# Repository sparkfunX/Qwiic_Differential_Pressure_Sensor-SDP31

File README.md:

SparkX Differential Pressure Sensor - SDP31 (Qwiic)
===================================================

[*SparkX Differential Pressure Sensor - SDP31 (Qwiic) (SPX-17874)*](https://www.sparkfun.com/products/17874)

The SDP3x sensor family is Sensirion’s series of small differential pressure sensors designed for high-volume applications
where size is a key requirement. It builds on the next generation CMOSens® sensor chip that is at the heart of Sensirion’s
new differential pressure and flow sensing platform.

The digital SDP31 sensor features fast measurement speed, excellent accuracy and long-term stability and has no zero-point
drift. Furthermore, it is reflow solderable and provides extended functionality, such as smart averaging, multiple temperature
compensation modes, configurable I2C address and interrupts.

Able to measure differential pressures in the range +/- 500 Pascals (+/- 0.005 Atm), the SDP31 is ideally suited to air flow rate
and air speed measurement. Need an air speed indicator for your drone or model aircraft? This could be the sensor for you!

Repository Contents
-------------------
* **/Documents** - datasheets etc.
* **/Hardware** - Eagle design files (.brd, .sch)

Documentation
--------------
* **[SDP3X Arduino Library](https://github.com/sparkfun/SparkFun_SDP3x_Arduino_Library)** - Arduino library for the SparkFun Differential Pressure Sensor - SDP31.
* **[Hookup Guide]()** - Basic hookup guide for the SparkX Differential Pressure Sensor - SDP31.

Product Versions
----------------
* [SPX-17874](https://www.sparkfun.com/products/17874) - Original SparkX Release.

License Information
-------------------

This product is _**open source**_!

Please review the LICENSE.md file for license information.

If you have any questions or concerns on licensing, please contact technical support on our [SparkFun forums](https://forum.sparkfun.com/viewforum.php?f=152).

Distributed as-is; no warranty is given.

- Your friends at SparkFun.

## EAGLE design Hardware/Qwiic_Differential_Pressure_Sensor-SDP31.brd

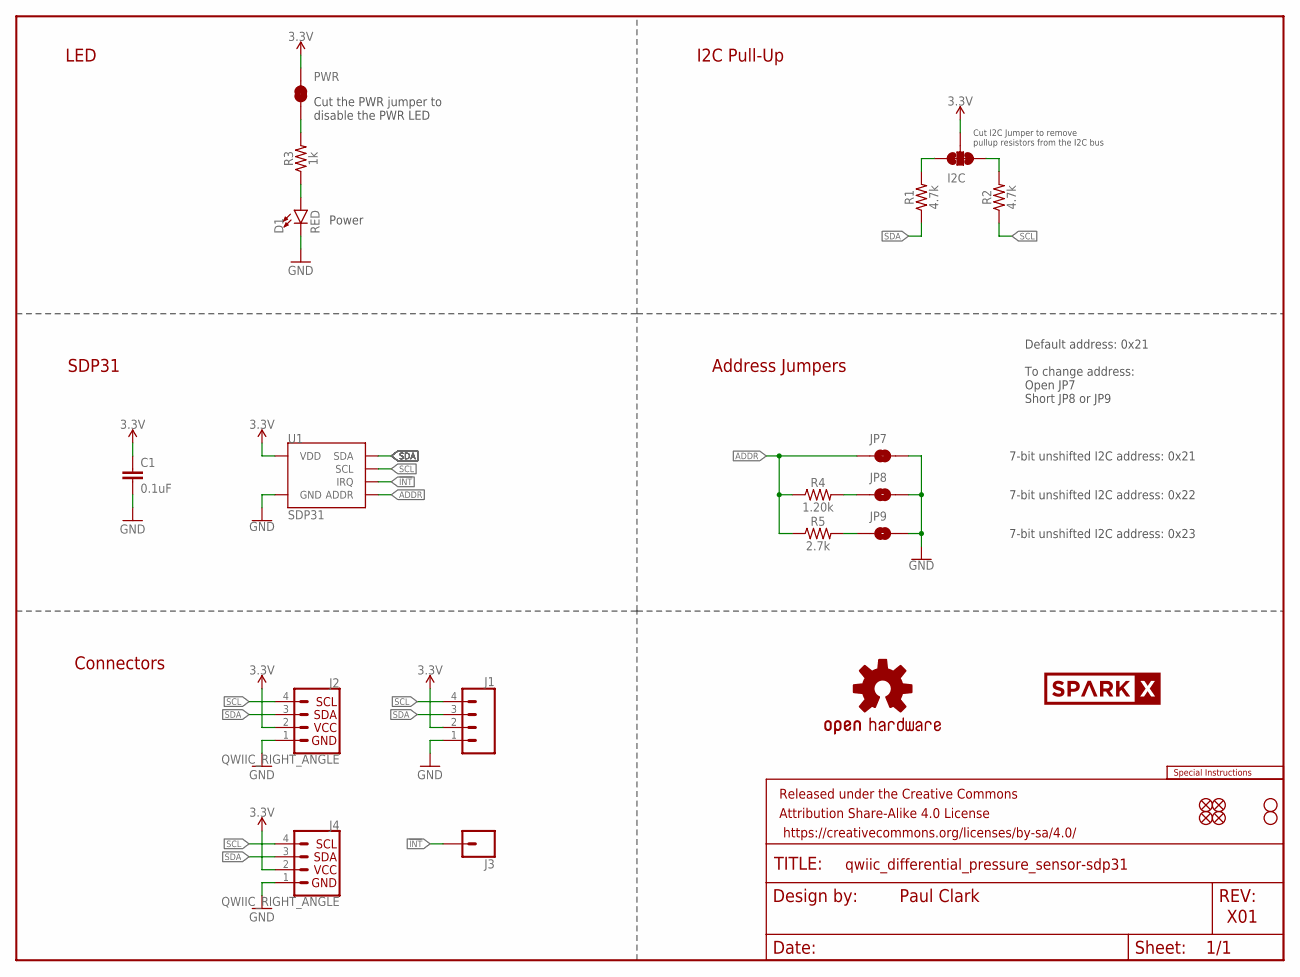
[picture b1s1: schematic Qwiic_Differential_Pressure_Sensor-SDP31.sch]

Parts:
C1: 0.1uF; 0603
D1: RED; LED-0603
FRAME1: FRAME-LETTER; CREATIVE_COMMONS
I2C: JUMPER-SMT_3_2-NC_TRACE_SILK; SMT-JUMPER_3_2-NC_TRACE_SILK
J1: CONN_041X04_NO_SILK; 1X04_NO_SILK
J2, J4: QWIIC_RIGHT_ANGLE; JST04_1MM_RA
J3: CONN_01PTH_NO_SILK_YES_STOP; 1X01_NO_SILK
JP1, JP2, JP5, JP6: FIDUCIALUFIDUCIAL; FIDUCIAL-MICRO
JP3, JP4: STAND-OFF
JP7: JUMPER-SMT_2_NC_TRACE_SILK; SMT-JUMPER_2_NC_TRACE_SILK
JP8, JP9: JUMPER-SMT_2_NO_SILK; SMT-JUMPER_2_NO_SILK
LOGO1: SPECIAL_INSTRUCTIONS-ORDERING; ORDERING_INSTRUCTIONS
LOGO5: OSHW-LOGOS; OSHW-LOGO-S
PWR: JUMPER-SMT_2_NC_TRACE_SILK; SMT-JUMPER_2_NC_TRACE_SILK
R1, R2: 4.7k; 0603
R3: 1k; 0603
R4: 1.20k; 0603
R5: 2.7k; 0603
U1: SDP31; SDP3X
U$18: SPARKX-LOGO3; SPARKX-SMALL

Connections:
3.3V: C1.1, I2C.2, J1.2, J2.2, J4.2, PWR.2, U1.7 (VDD)
!INT!: J3.1, U1.4 (IRQ)
ADDR: JP7.1, R4.1, R5.1, U1.9 (ADDR)
GND: C1.2, D1.C, J1.1, J2.1, J4.1, JP7.2, JP8.2, JP9.2, U1.1 (GND), U1.2 (GND), U1.3 (GND), U1.6 (GND), U1.10 (GND), U1.11 (GND), U1.DIEPAD1 (GND), U1.DIEPAD2 (GND)
unnamed: PWR.1, R3.2
unnamed: I2C.3, R1.2
unnamed: D1.A, R3.1
unnamed: I2C.1, R2.2
unnamed: JP8.1, R4.2
unnamed: JP9.1, R5.2
SCL: J1.4, J2.4, J4.4, R2.1, U1.5 (SCL)
SDA: J1.3, J2.3, J4.3, R1.1, U1.8 (SDA)

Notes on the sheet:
Paul Clark
X01
7-bit unshifted I2C address: 0x21
Power
I2C Pull-Up
SDP31
Connectors
Cut the PWR jumper to disable the PWR LED
Cut I2C Jumper to remove pullup resistors from the I2C bus
LED
Address Jumpers
7-bit unshifted I2C address: 0x22
7-bit unshifted I2C address: 0x23
Default address: 0x21 To change address: Open JP7 Short JP8 or JP9

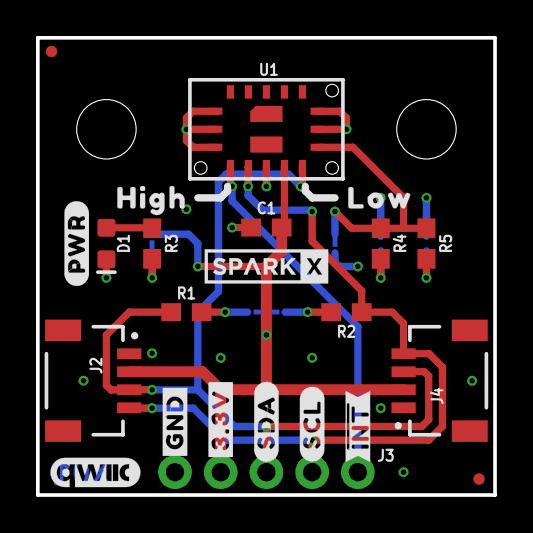
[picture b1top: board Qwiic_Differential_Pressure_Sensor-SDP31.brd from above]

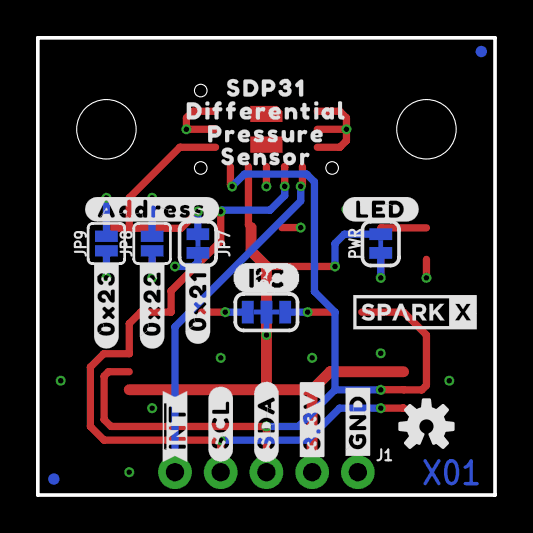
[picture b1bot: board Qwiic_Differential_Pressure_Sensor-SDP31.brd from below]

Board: 4 copper layers, 25.4 x 25.4 mm, 52 parts (25 on the bottom side), 12 nets.

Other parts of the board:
U$1, U$33: #GND#0
U$2, U$34: #3#3V#0
U$3, U$35: #SDA#0
U$4, U$36: #SCL#0
U$5, U$6: ##INT##0
U$7: #0X21#0
U$8: #0X22#0
U$9: #0X23#0
U$10: DIFFERENTIAL0
U$11: PRESSURE0
U$12: SENSOR0
U$13: SDP310
U$14: #LED#0
U$15: I2C
U$16: QWIIC_5MM
U$17: HIGH0
U$19: LOW0
U$20: SPARKX-LOGO3; SPARKX-SMALL
U$21: #ADDRESS#0
U$32: #PWR#0

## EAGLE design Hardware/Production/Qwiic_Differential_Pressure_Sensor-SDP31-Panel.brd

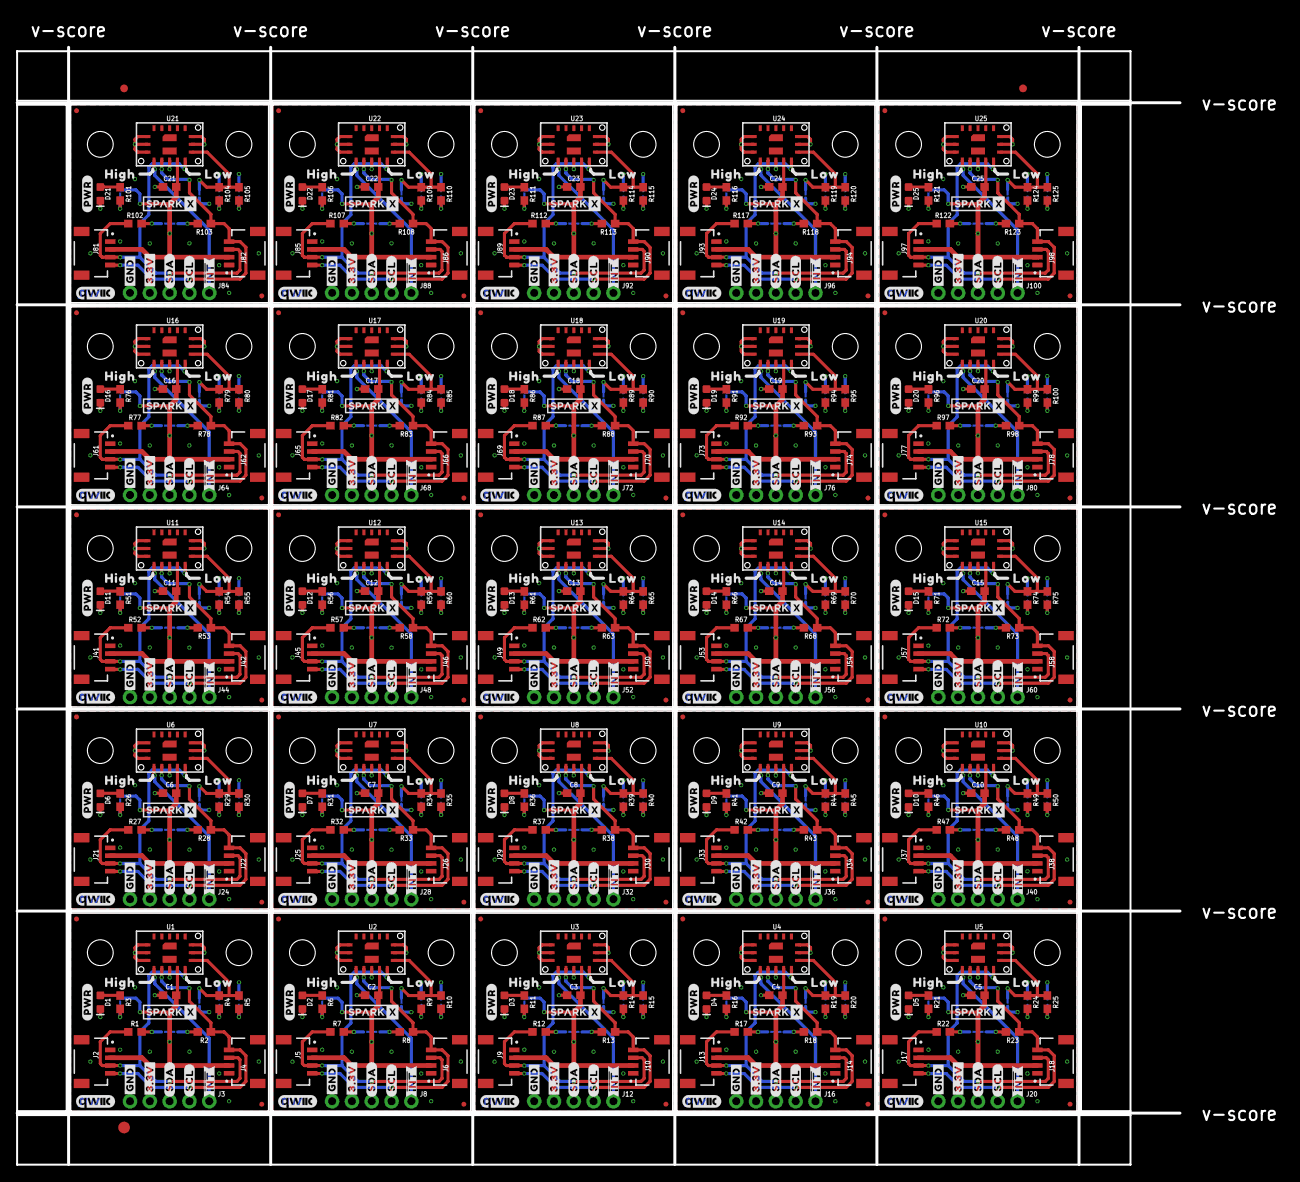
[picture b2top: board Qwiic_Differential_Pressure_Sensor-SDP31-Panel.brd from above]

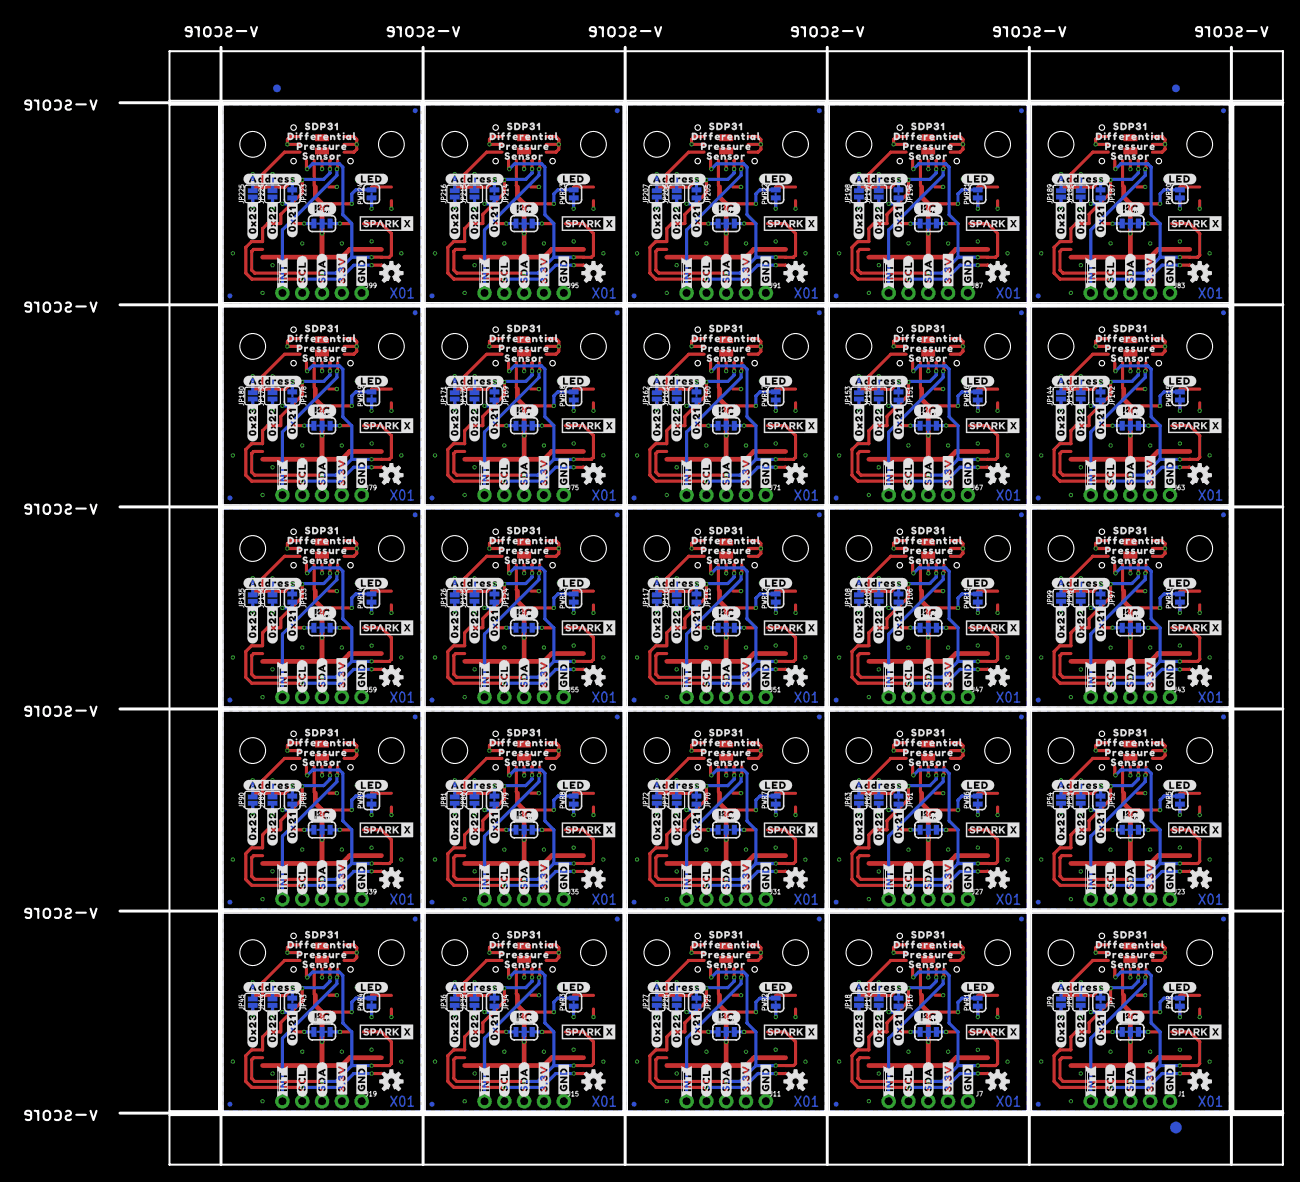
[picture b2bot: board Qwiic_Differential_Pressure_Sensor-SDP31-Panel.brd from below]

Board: 4 copper layers, 162.3 x 147.1 mm, 1256 parts (628 on the bottom side), 300 nets.

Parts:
C1, C2, C3, C4, C5, C6, C7, C8, C9, C10, C11, C12, C13, C14, C15, C16, C17, C18, C19, C20, C21, C22, C23, C24, C25: 0.1uF; 0603
D1, D2, D3, D4, D5, D6, D7, D8, D9, D10, D11, D12, D13, D14, D15, D16, D17, D18, D19, D20, D21, D22, D23, D24, D25: RED; LED-0603
E$1, E$2, E$3, E$4: FIDUCIAL-1X2
E$5, E$6: FIDUCIAL-1.5X3
I2C, I2C1, I2C2, I2C3, I2C4, I2C5, I2C6, I2C7, I2C8, I2C9, I2C10, I2C11, I2C12, I2C13, I2C14, I2C15, I2C16, I2C17, I2C18, I2C19, I2C20, I2C21, I2C22, I2C23, I2C24: JUMPER-SMT_3_2-NC_TRACE_SILK; SMT-JUMPER_3_2-NC_TRACE_SILK
J1, J7, J11, J15, J19, J23, J27, J31, J35, J39, J43, J47, J51, J55, J59, J63, J67, J71, J75, J79, J83, J87, J91, J95, J99: 1X04_NO_SILK
J2, J4, J5, J6, J9, J10, J13, J14, J17, J18, J21, J22, J25, J26, J29, J30, J33, J34, J37, J38, J41, J42, J45, J46, J49, J50, J53, J54, J57, J58, J61, J62, J65, J66, J69, J70, J73, J74, J77, J78, J81, J82, J85, J86, J89, J90, J93, J94, J97, J98: QWIIC_RIGHT_ANGLE; JST04_1MM_RA
J3, J8, J12, J16, J20, J24, J28, J32, J36, J40, J44, J48, J52, J56, J60, J64, J68, J72, J76, J80, J84, J88, J92, J96, J100: 1X01_NO_SILK
JP1, JP2, JP5, JP6, JP12, JP13, JP14, JP15, JP21, JP22, JP23, JP24, JP30, JP31, JP32, JP33, JP39, JP40, JP41, JP42, JP48, JP49, JP50, JP51, JP57, JP58, JP59, JP60, JP66, JP67, JP68, JP69, JP75, JP76, JP77, JP78, JP84, JP85, JP86, JP87, JP93, JP94, JP95, JP96, JP102, JP103, JP104, JP105, JP111, JP112, JP113, JP114, JP120, JP121, JP122, JP123, JP129, JP130, JP131, JP132, JP138, JP139, JP140, JP141, JP147, JP148, JP149, JP150, JP156, JP157, JP158, JP159, JP165, JP166, JP167, JP168, JP174, JP175, JP176, JP177, JP183, JP184, JP185, JP186, JP192, JP193, JP194, JP195, JP201, JP202, JP203, JP204, JP210, JP211, JP212, JP213, JP219, JP220, JP221, JP222: FIDUCIALUFIDUCIAL; FIDUCIAL-MICRO
JP3, JP4, JP10, JP11, JP19, JP20, JP28, JP29, JP37, JP38, JP46, JP47, JP55, JP56, JP64, JP65, JP73, JP74, JP82, JP83, JP91, JP92, JP100, JP101, JP109, JP110, JP118, JP119, JP127, JP128, JP136, JP137, JP145, JP146, JP154, JP155, JP163, JP164, JP172, JP173, JP181, JP182, JP190, JP191, JP199, JP200, JP208, JP209, JP217, JP218: STAND-OFF
JP7, JP16, JP25, JP34, JP43, JP52, JP61, JP70, JP79, JP88, JP97, JP106, JP115, JP124, JP133, JP142, JP151, JP160, JP169, JP178, JP187, JP196, JP205, JP214, JP223: JUMPER-SMT_2_NC_TRACE_SILK; SMT-JUMPER_2_NC_TRACE_SILK
JP8, JP9, JP17, JP18, JP26, JP27, JP35, JP36, JP44, JP45, JP53, JP54, JP62, JP63, JP71, JP72, JP80, JP81, JP89, JP90, JP98, JP99, JP107, JP108, JP116, JP117, JP125, JP126, JP134, JP135, JP143, JP144, JP152, JP153, JP161, JP162, JP170, JP171, JP179, JP180, JP188, JP189, JP197, JP198, JP206, JP207, JP215, JP216, JP224, JP225: JUMPER-SMT_2_NO_SILK; SMT-JUMPER_2_NO_SILK
LOGO1, LOGO2, LOGO3, LOGO4, LOGO5, LOGO6, LOGO7, LOGO8, LOGO9, LOGO10, LOGO11, LOGO12, LOGO13, LOGO14, LOGO15, LOGO16, LOGO17, LOGO18, LOGO19, LOGO20, LOGO21, LOGO22, LOGO23, LOGO24, LOGO25: OSHW-LOGOS; OSHW-LOGO-S
PWR, PWR1, PWR2, PWR3, PWR4, PWR5, PWR6, PWR7, PWR8, PWR9, PWR10, PWR11, PWR12, PWR13, PWR14, PWR15, PWR16, PWR17, PWR18, PWR19, PWR20, PWR21, PWR22, PWR23, PWR24: JUMPER-SMT_2_NC_TRACE_SILK; SMT-JUMPER_2_NC_TRACE_SILK
R1, R2, R7, R8, R12, R13, R17, R18, R22, R23, R27, R28, R32, R33, R37, R38, R42, R43, R47, R48, R52, R53, R57, R58, R62, R63, R67, R68, R72, R73, R77, R78, R82, R83, R87, R88, R92, R93, R97, R98, R102, R103, R107, R108, R112, R113, R117, R118, R122, R123: 4.7k; 0603
R3, R6, R11, R16, R21, R26, R31, R36, R41, R46, R51, R56, R61, R66, R71, R76, R81, R86, R91, R96, R101, R106, R111, R116, R121: 1k; 0603
R4, R9, R14, R19, R24, R29, R34, R39, R44, R49, R54, R59, R64, R69, R74, R79, R84, R89, R94, R99, R104, R109, R114, R119, R124: 1.20k; 0603
R5, R10, R15, R20, R25, R30, R35, R40, R45, R50, R55, R60, R65, R70, R75, R80, R85, R90, R95, R100, R105, R110, R115, R120, R125: 2.7k; 0603
U1, U2, U3, U4, U5, U6, U7, U8, U9, U10, U11, U12, U13, U14, U15, U16, U17, U18, U19, U20, U21, U22, U23, U24, U25: SDP31; SDP3X
U$1, U$26, U$30, U$33, U$57, U$61, U$83, U$87, U$109, U$113, U$135, U$139, U$161, U$165, U$187, U$191, U$213, U$217, U$239, U$243, U$265, U$269, U$291, U$295, U$317, U$321, U$343, U$347, U$369, U$373, U$395, U$399, U$421, U$425, U$447, U$451, U$473, U$477, U$499, U$503, U$525, U$529, U$551, U$555, U$577, U$581, U$603, U$607, U$629, U$633: #GND#0
U$2, U$27, U$31, U$34, U$58, U$62, U$84, U$88, U$110, U$114, U$136, U$140, U$162, U$166, U$188, U$192, U$214, U$218, U$240, U$244, U$266, U$270, U$292, U$296, U$318, U$322, U$344, U$348, U$370, U$374, U$396, U$400, U$422, U$426, U$448, U$452, U$474, U$478, U$500, U$504, U$526, U$530, U$552, U$556, U$578, U$582, U$604, U$608, U$630, U$634: #3#3V#0
U$3, U$28, U$35, U$37, U$59, U$63, U$85, U$89, U$111, U$115, U$137, U$141, U$163, U$167, U$189, U$193, U$215, U$219, U$241, U$245, U$267, U$271, U$293, U$297, U$319, U$323, U$345, U$349, U$371, U$375, U$397, U$401, U$423, U$427, U$449, U$453, U$475, U$479, U$501, U$505, U$527, U$531, U$553, U$557, U$579, U$583, U$605, U$609, U$631, U$635: #SDA#0
U$4, U$29, U$36, U$38, U$60, U$64, U$86, U$90, U$112, U$116, U$138, U$142, U$164, U$168, U$190, U$194, U$216, U$220, U$242, U$246, U$268, U$272, U$294, U$298, U$320, U$324, U$346, U$350, U$372, U$376, U$398, U$402, U$424, U$428, U$450, U$454, U$476, U$480, U$502, U$506, U$528, U$532, U$554, U$558, U$580, U$584, U$606, U$610, U$632, U$636: #SCL#0
U$5, U$6, U$50, U$51, U$76, U$77, U$102, U$103, U$128, U$129, U$154, U$155, U$180, U$181, U$206, U$207, U$232, U$233, U$258, U$259, U$284, U$285, U$310, U$311, U$336, U$337, U$362, U$363, U$388, U$389, U$414, U$415, U$440, U$441, U$466, U$467, U$492, U$493, U$518, U$519, U$544, U$545, U$570, U$571, U$596, U$597, U$622, U$623, U$648, U$649: ##INT##0
U$7, U$39, U$65, U$91, U$117, U$143, U$169, U$195, U$221, U$247, U$273, U$299, U$325, U$351, U$377, U$403, U$429, U$455, U$481, U$507, U$533, U$559, U$585, U$611, U$637: #0X21#0
U$8, U$40, U$66, U$92, U$118, U$144, U$170, U$196, U$222, U$248, U$274, U$300, U$326, U$352, U$378, U$404, U$430, U$456, U$482, U$508, U$534, U$560, U$586, U$612, U$638: #0X22#0
U$9, U$41, U$67, U$93, U$119, U$145, U$171, U$197, U$223, U$249, U$275, U$301, U$327, U$353, U$379, U$405, U$431, U$457, U$483, U$509, U$535, U$561, U$587, U$613, U$639: #0X23#0
U$10, U$42, U$68, U$94, U$120, U$146, U$172, U$198, U$224, U$250, U$276, U$302, U$328, U$354, U$380, U$406, U$432, U$458, U$484, U$510, U$536, U$562, U$588, U$614, U$640: DIFFERENTIAL0
U$11, U$43, U$69, U$95, U$121, U$147, U$173, U$199, U$225, U$251, U$277, U$303, U$329, U$355, U$381, U$407, U$433, U$459, U$485, U$511, U$537, U$563, U$589, U$615, U$641: PRESSURE0
U$12, U$44, U$70, U$96, U$122, U$148, U$174, U$200, U$226, U$252, U$278, U$304, U$330, U$356, U$382, U$408, U$434, U$460, U$486, U$512, U$538, U$564, U$590, U$616, U$642: SENSOR0
U$13, U$45, U$71, U$97, U$123, U$149, U$175, U$201, U$227, U$253, U$279, U$305, U$331, U$357, U$383, U$409, U$435, U$461, U$487, U$513, U$539, U$565, U$591, U$617, U$643: SDP310
U$14, U$46, U$72, U$98, U$124, U$150, U$176, U$202, U$228, U$254, U$280, U$306, U$332, U$358, U$384, U$410, U$436, U$462, U$488, U$514, U$540, U$566, U$592, U$618, U$644: #LED#0
U$15, U$22, U$53, U$79, U$105, U$131, U$157, U$183, U$209, U$235, U$261, U$287, U$313, U$339, U$365, U$391, U$417, U$443, U$469, U$495, U$521, U$547, U$573, U$599, U$625: I2C
U$16, U$23, U$54, U$80, U$106, U$132, U$158, U$184, U$210, U$236, U$262, U$288, U$314, U$340, U$366, U$392, U$418, U$444, U$470, U$496, U$522, U$548, U$574, U$600, U$626: QWIIC_5MM
U$17, U$47, U$73, U$99, U$125, U$151, U$177, U$203, U$229, U$255, U$281, U$307, U$333, U$359, U$385, U$411, U$437, U$463, U$489, U$515, U$541, U$567, U$593, U$619, U$645: HIGH0
U$18, U$20, U$24, U$49, U$55, U$75, U$81, U$101, U$107, U$127, U$133, U$153, U$159, U$179, U$185, U$205, U$211, U$231, U$237, U$257, U$263, U$283, U$289, U$309, U$315, U$335, U$341, U$361, U$367, U$387, U$393, U$413, U$419, U$439, U$445, U$465, U$471, U$491, U$497, U$517, U$523, U$543, U$549, U$569, U$575, U$595, U$601, U$621, U$627, U$647: SPARKX-LOGO3; SPARKX-SMALL
U$19, U$48, U$74, U$100, U$126, U$152, U$178, U$204, U$230, U$256, U$282, U$308, U$334, U$360, U$386, U$412, U$438, U$464, U$490, U$516, U$542, U$568, U$594, U$620, U$646: LOW0
U$21, U$52, U$78, U$104, U$130, U$156, U$182, U$208, U$234, U$260, U$286, U$312, U$338, U$364, U$390, U$416, U$442, U$468, U$494, U$520, U$546, U$572, U$598, U$624, U$650: #ADDRESS#0
U$25, U$32, U$56, U$82, U$108, U$134, U$160, U$186, U$212, U$238, U$264, U$290, U$316, U$342, U$368, U$394, U$420, U$446, U$472, U$498, U$524, U$550, U$576, U$602, U$628: #PWR#0

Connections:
3.3V: C1.1, I2C.2, J1.2, J2.2, J4.2, PWR.2, U1.7
3.3V1: C2.1, I2C1.2, J5.2, J6.2, J7.2, PWR1.2, U2.7
3.3V2: C3.1, I2C2.2, J9.2, J10.2, J11.2, PWR2.2, U3.7
3.3V3: C4.1, I2C3.2, J13.2, J14.2, J15.2, PWR3.2, U4.7
3.3V4: C5.1, I2C4.2, J17.2, J18.2, J19.2, PWR4.2, U5.7
3.3V5: C6.1, I2C5.2, J21.2, J22.2, J23.2, PWR5.2, U6.7
3.3V6: C7.1, I2C6.2, J25.2, J26.2, J27.2, PWR6.2, U7.7
3.3V7: C8.1, I2C7.2, J29.2, J30.2, J31.2, PWR7.2, U8.7
3.3V8: C9.1, I2C8.2, J33.2, J34.2, J35.2, PWR8.2, U9.7
3.3V9: C10.1, I2C9.2, J37.2, J38.2, J39.2, PWR9.2, U10.7
3.3V10: C11.1, I2C10.2, J41.2, J42.2, J43.2, PWR10.2, U11.7
3.3V11: C12.1, I2C11.2, J45.2, J46.2, J47.2, PWR11.2, U12.7
3.3V12: C13.1, I2C12.2, J49.2, J50.2, J51.2, PWR12.2, U13.7
3.3V13: C14.1, I2C13.2, J53.2, J54.2, J55.2, PWR13.2, U14.7
3.3V14: C15.1, I2C14.2, J57.2, J58.2, J59.2, PWR14.2, U15.7
3.3V15: C16.1, I2C15.2, J61.2, J62.2, J63.2, PWR15.2, U16.7
3.3V16: C17.1, I2C16.2, J65.2, J66.2, J67.2, PWR16.2, U17.7
3.3V17: C18.1, I2C17.2, J69.2, J70.2, J71.2, PWR17.2, U18.7
3.3V18: C19.1, I2C18.2, J73.2, J74.2, J75.2, PWR18.2, U19.7
3.3V19: C20.1, I2C19.2, J77.2, J78.2, J79.2, PWR19.2, U20.7
3.3V20: C21.1, I2C20.2, J81.2, J82.2, J83.2, PWR20.2, U21.7
3.3V21: C22.1, I2C21.2, J85.2, J86.2, J87.2, PWR21.2, U22.7
3.3V22: C23.1, I2C22.2, J89.2, J90.2, J91.2, PWR22.2, U23.7
3.3V23: C24.1, I2C23.2, J93.2, J94.2, J95.2, PWR23.2, U24.7
3.3V24: C25.1, I2C24.2, J97.2, J98.2, J99.2, PWR24.2, U25.7
!INT!: J3.1, U1.4
!INT!1: J8.1, U2.4
!INT!2: J12.1, U3.4
!INT!3: J16.1, U4.4
!INT!4: J20.1, U5.4
!INT!5: J24.1, U6.4
!INT!6: J28.1, U7.4
!INT!7: J32.1, U8.4
!INT!8: J36.1, U9.4
!INT!9: J40.1, U10.4
!INT!10: J44.1, U11.4
!INT!11: J48.1, U12.4
!INT!12: J52.1, U13.4
!INT!13: J56.1, U14.4
!INT!14: J60.1, U15.4
!INT!15: J64.1, U16.4
!INT!16: J68.1, U17.4
!INT!17: J72.1, U18.4
!INT!18: J76.1, U19.4
!INT!19: J80.1, U20.4
!INT!20: J84.1, U21.4
!INT!21: J88.1, U22.4
!INT!22: J92.1, U23.4
!INT!23: J96.1, U24.4
!INT!24: J100.1, U25.4
ADDR: JP7.1, R4.1, R5.1, U1.9
ADDR1: JP16.1, R9.1, R10.1, U2.9
ADDR2: JP25.1, R14.1, R15.1, U3.9
ADDR3: JP34.1, R19.1, R20.1, U4.9
ADDR4: JP43.1, R24.1, R25.1, U5.9
ADDR5: JP52.1, R29.1, R30.1, U6.9
ADDR6: JP61.1, R34.1, R35.1, U7.9
ADDR7: JP70.1, R39.1, R40.1, U8.9
ADDR8: JP79.1, R44.1, R45.1, U9.9
ADDR9: JP88.1, R49.1, R50.1, U10.9
ADDR10: JP97.1, R54.1, R55.1, U11.9
ADDR11: JP106.1, R59.1, R60.1, U12.9
ADDR12: JP115.1, R64.1, R65.1, U13.9
ADDR13: JP124.1, R69.1, R70.1, U14.9
ADDR14: JP133.1, R74.1, R75.1, U15.9
ADDR15: JP142.1, R79.1, R80.1, U16.9
ADDR16: JP151.1, R84.1, R85.1, U17.9
ADDR17: JP160.1, R89.1, R90.1, U18.9
ADDR18: JP169.1, R94.1, R95.1, U19.9
ADDR19: JP178.1, R99.1, R100.1, U20.9
ADDR20: JP187.1, R104.1, R105.1, U21.9
ADDR21: JP196.1, R109.1, R110.1, U22.9
ADDR22: JP205.1, R114.1, R115.1, U23.9
ADDR23: JP214.1, R119.1, R120.1, U24.9
ADDR24: JP223.1, R124.1, R125.1, U25.9
GND: C1.2, D1.C, J1.1, J2.1, J4.1, JP7.2, JP8.2, JP9.2, U1.1, U1.2, U1.3, U1.6, U1.10, U1.11, U1.DIEPAD1, U1.DIEPAD2
GND1: C2.2, D2.C, J5.1, J6.1, J7.1, JP16.2, JP17.2, JP18.2, U2.1, U2.2, U2.3, U2.6, U2.10, U2.11, U2.DIEPAD1, U2.DIEPAD2
GND2: C3.2, D3.C, J9.1, J10.1, J11.1, JP25.2, JP26.2, JP27.2, U3.1, U3.2, U3.3, U3.6, U3.10, U3.11, U3.DIEPAD1, U3.DIEPAD2
GND3: C4.2, D4.C, J13.1, J14.1, J15.1, JP34.2, JP35.2, JP36.2, U4.1, U4.2, U4.3, U4.6, U4.10, U4.11, U4.DIEPAD1, U4.DIEPAD2
GND4: C5.2, D5.C, J17.1, J18.1, J19.1, JP43.2, JP44.2, JP45.2, U5.1, U5.2, U5.3, U5.6, U5.10, U5.11, U5.DIEPAD1, U5.DIEPAD2
GND5: C6.2, D6.C, J21.1, J22.1, J23.1, JP52.2, JP53.2, JP54.2, U6.1, U6.2, U6.3, U6.6, U6.10, U6.11, U6.DIEPAD1, U6.DIEPAD2
GND6: C7.2, D7.C, J25.1, J26.1, J27.1, JP61.2, JP62.2, JP63.2, U7.1, U7.2, U7.3, U7.6, U7.10, U7.11, U7.DIEPAD1, U7.DIEPAD2
GND7: C8.2, D8.C, J29.1, J30.1, J31.1, JP70.2, JP71.2, JP72.2, U8.1, U8.2, U8.3, U8.6, U8.10, U8.11, U8.DIEPAD1, U8.DIEPAD2
GND8: C9.2, D9.C, J33.1, J34.1, J35.1, JP79.2, JP80.2, JP81.2, U9.1, U9.2, U9.3, U9.6, U9.10, U9.11, U9.DIEPAD1, U9.DIEPAD2
GND9: C10.2, D10.C, J37.1, J38.1, J39.1, JP88.2, JP89.2, JP90.2, U10.1, U10.2, U10.3, U10.6, U10.10, U10.11, U10.DIEPAD1, U10.DIEPAD2
GND10: C11.2, D11.C, J41.1, J42.1, J43.1, JP97.2, JP98.2, JP99.2, U11.1, U11.2, U11.3, U11.6, U11.10, U11.11, U11.DIEPAD1, U11.DIEPAD2
GND11: C12.2, D12.C, J45.1, J46.1, J47.1, JP106.2, JP107.2, JP108.2, U12.1, U12.2, U12.3, U12.6, U12.10, U12.11, U12.DIEPAD1, U12.DIEPAD2
GND12: C13.2, D13.C, J49.1, J50.1, J51.1, JP115.2, JP116.2, JP117.2, U13.1, U13.2, U13.3, U13.6, U13.10, U13.11, U13.DIEPAD1, U13.DIEPAD2
GND13: C14.2, D14.C, J53.1, J54.1, J55.1, JP124.2, JP125.2, JP126.2, U14.1, U14.2, U14.3, U14.6, U14.10, U14.11, U14.DIEPAD1, U14.DIEPAD2
GND14: C15.2, D15.C, J57.1, J58.1, J59.1, JP133.2, JP134.2, JP135.2, U15.1, U15.2, U15.3, U15.6, U15.10, U15.11, U15.DIEPAD1, U15.DIEPAD2
GND15: C16.2, D16.C, J61.1, J62.1, J63.1, JP142.2, JP143.2, JP144.2, U16.1, U16.2, U16.3, U16.6, U16.10, U16.11, U16.DIEPAD1, U16.DIEPAD2
GND16: C17.2, D17.C, J65.1, J66.1, J67.1, JP151.2, JP152.2, JP153.2, U17.1, U17.2, U17.3, U17.6, U17.10, U17.11, U17.DIEPAD1, U17.DIEPAD2
GND17: C18.2, D18.C, J69.1, J70.1, J71.1, JP160.2, JP161.2, JP162.2, U18.1, U18.2, U18.3, U18.6, U18.10, U18.11, U18.DIEPAD1, U18.DIEPAD2
GND18: C19.2, D19.C, J73.1, J74.1, J75.1, JP169.2, JP170.2, JP171.2, U19.1, U19.2, U19.3, U19.6, U19.10, U19.11, U19.DIEPAD1, U19.DIEPAD2
GND19: C20.2, D20.C, J77.1, J78.1, J79.1, JP178.2, JP179.2, JP180.2, U20.1, U20.2, U20.3, U20.6, U20.10, U20.11, U20.DIEPAD1, U20.DIEPAD2
GND20: C21.2, D21.C, J81.1, J82.1, J83.1, JP187.2, JP188.2, JP189.2, U21.1, U21.2, U21.3, U21.6, U21.10, U21.11, U21.DIEPAD1, U21.DIEPAD2
GND21: C22.2, D22.C, J85.1, J86.1, J87.1, JP196.2, JP197.2, JP198.2, U22.1, U22.2, U22.3, U22.6, U22.10, U22.11, U22.DIEPAD1, U22.DIEPAD2
GND22: C23.2, D23.C, J89.1, J90.1, J91.1, JP205.2, JP206.2, JP207.2, U23.1, U23.2, U23.3, U23.6, U23.10, U23.11, U23.DIEPAD1, U23.DIEPAD2
GND23: C24.2, D24.C, J93.1, J94.1, J95.1, JP214.2, JP215.2, JP216.2, U24.1, U24.2, U24.3, U24.6, U24.10, U24.11, U24.DIEPAD1, U24.DIEPAD2
GND24: C25.2, D25.C, J97.1, J98.1, J99.1, JP223.2, JP224.2, JP225.2, U25.1, U25.2, U25.3, U25.6, U25.10, U25.11, U25.DIEPAD1, U25.DIEPAD2
unnamed: PWR.1, R3.2
unnamed: I2C.3, R1.2
unnamed: D1.A, R3.1
unnamed: I2C.1, R2.2
unnamed: JP8.1, R4.2
unnamed: JP9.1, R5.2
unnamed: D2.A, R6.1
unnamed: PWR1.1, R6.2
unnamed: I2C1.3, R7.2
unnamed: I2C1.1, R8.2
unnamed: JP17.1, R9.2
unnamed: JP18.1, R10.2
unnamed: D3.A, R11.1
unnamed: PWR2.1, R11.2
unnamed: I2C2.3, R12.2
unnamed: I2C2.1, R13.2
unnamed: JP26.1, R14.2
unnamed: JP27.1, R15.2
unnamed: D4.A, R16.1
unnamed: PWR3.1, R16.2
unnamed: I2C3.3, R17.2
unnamed: I2C3.1, R18.2
unnamed: JP35.1, R19.2
unnamed: JP36.1, R20.2
unnamed: D5.A, R21.1
unnamed: PWR4.1, R21.2
unnamed: I2C4.3, R22.2
unnamed: I2C4.1, R23.2
unnamed: JP44.1, R24.2
unnamed: JP45.1, R25.2
unnamed: D6.A, R26.1
unnamed: PWR5.1, R26.2
unnamed: I2C5.3, R27.2
unnamed: I2C5.1, R28.2
unnamed: JP53.1, R29.2
unnamed: JP54.1, R30.2
unnamed: D7.A, R31.1
unnamed: PWR6.1, R31.2
unnamed: I2C6.3, R32.2
unnamed: I2C6.1, R33.2
unnamed: JP62.1, R34.2
unnamed: JP63.1, R35.2
unnamed: D8.A, R36.1
unnamed: PWR7.1, R36.2
unnamed: I2C7.3, R37.2
unnamed: I2C7.1, R38.2
unnamed: JP71.1, R39.2
unnamed: JP72.1, R40.2
unnamed: D9.A, R41.1
unnamed: PWR8.1, R41.2
unnamed: I2C8.3, R42.2
unnamed: I2C8.1, R43.2
unnamed: JP80.1, R44.2
unnamed: JP81.1, R45.2
unnamed: D10.A, R46.1
unnamed: PWR9.1, R46.2
unnamed: I2C9.3, R47.2
unnamed: I2C9.1, R48.2
unnamed: JP89.1, R49.2
unnamed: JP90.1, R50.2
unnamed: D11.A, R51.1
unnamed: PWR10.1, R51.2
unnamed: I2C10.3, R52.2
unnamed: I2C10.1, R53.2
unnamed: JP98.1, R54.2
unnamed: JP99.1, R55.2
unnamed: D12.A, R56.1
unnamed: PWR11.1, R56.2
unnamed: I2C11.3, R57.2
unnamed: I2C11.1, R58.2
unnamed: JP107.1, R59.2
unnamed: JP108.1, R60.2
unnamed: D13.A, R61.1
unnamed: PWR12.1, R61.2
unnamed: I2C12.3, R62.2
unnamed: I2C12.1, R63.2
unnamed: JP116.1, R64.2
unnamed: JP117.1, R65.2
unnamed: D14.A, R66.1
unnamed: PWR13.1, R66.2
unnamed: I2C13.3, R67.2
unnamed: I2C13.1, R68.2
unnamed: JP125.1, R69.2
unnamed: JP126.1, R70.2
unnamed: D15.A, R71.1
unnamed: PWR14.1, R71.2
unnamed: I2C14.3, R72.2
unnamed: I2C14.1, R73.2
unnamed: JP134.1, R74.2
unnamed: JP135.1, R75.2
unnamed: D16.A, R76.1
unnamed: PWR15.1, R76.2
unnamed: I2C15.3, R77.2
unnamed: I2C15.1, R78.2
unnamed: JP143.1, R79.2
unnamed: JP144.1, R80.2
unnamed: D17.A, R81.1
unnamed: PWR16.1, R81.2
unnamed: I2C16.3, R82.2
unnamed: I2C16.1, R83.2
unnamed: JP152.1, R84.2
unnamed: JP153.1, R85.2
unnamed: D18.A, R86.1
unnamed: PWR17.1, R86.2
unnamed: I2C17.3, R87.2
unnamed: I2C17.1, R88.2
unnamed: JP161.1, R89.2
unnamed: JP162.1, R90.2
unnamed: D19.A, R91.1
unnamed: PWR18.1, R91.2
unnamed: I2C18.3, R92.2
unnamed: I2C18.1, R93.2
unnamed: JP170.1, R94.2
unnamed: JP171.1, R95.2
unnamed: D20.A, R96.1
unnamed: PWR19.1, R96.2
unnamed: I2C19.3, R97.2
unnamed: I2C19.1, R98.2
unnamed: JP179.1, R99.2
unnamed: JP180.1, R100.2
unnamed: D21.A, R101.1
unnamed: PWR20.1, R101.2
unnamed: I2C20.3, R102.2
unnamed: I2C20.1, R103.2
unnamed: JP188.1, R104.2
unnamed: JP189.1, R105.2
unnamed: D22.A, R106.1
unnamed: PWR21.1, R106.2
unnamed: I2C21.3, R107.2
unnamed: I2C21.1, R108.2
unnamed: JP197.1, R109.2
unnamed: JP198.1, R110.2
unnamed: D23.A, R111.1
unnamed: PWR22.1, R111.2
unnamed: I2C22.3, R112.2
unnamed: I2C22.1, R113.2
unnamed: JP206.1, R114.2
unnamed: JP207.1, R115.2
unnamed: D24.A, R116.1
unnamed: PWR23.1, R116.2
unnamed: I2C23.3, R117.2
unnamed: I2C23.1, R118.2
unnamed: JP215.1, R119.2
unnamed: JP216.1, R120.2
unnamed: D25.A, R121.1
unnamed: PWR24.1, R121.2
unnamed: I2C24.3, R122.2
unnamed: I2C24.1, R123.2
unnamed: JP224.1, R124.2
unnamed: JP225.1, R125.2
SCL: J1.4, J2.4, J4.4, R2.1, U1.5
SCL1: J5.4, J6.4, J7.4, R8.1, U2.5
SCL2: J9.4, J10.4, J11.4, R13.1, U3.5
SCL3: J13.4, J14.4, J15.4, R18.1, U4.5
SCL4: J17.4, J18.4, J19.4, R23.1, U5.5
SCL5: J21.4, J22.4, J23.4, R28.1, U6.5
SCL6: J25.4, J26.4, J27.4, R33.1, U7.5
SCL7: J29.4, J30.4, J31.4, R38.1, U8.5
SCL8: J33.4, J34.4, J35.4, R43.1, U9.5
SCL9: J37.4, J38.4, J39.4, R48.1, U10.5
SCL10: J41.4, J42.4, J43.4, R53.1, U11.5
SCL11: J45.4, J46.4, J47.4, R58.1, U12.5
SCL12: J49.4, J50.4, J51.4, R63.1, U13.5
SCL13: J53.4, J54.4, J55.4, R68.1, U14.5
SCL14: J57.4, J58.4, J59.4, R73.1, U15.5
SCL15: J61.4, J62.4, J63.4, R78.1, U16.5
SCL16: J65.4, J66.4, J67.4, R83.1, U17.5
SCL17: J69.4, J70.4, J71.4, R88.1, U18.5
SCL18: J73.4, J74.4, J75.4, R93.1, U19.5
SCL19: J77.4, J78.4, J79.4, R98.1, U20.5
SCL20: J81.4, J82.4, J83.4, R103.1, U21.5
SCL21: J85.4, J86.4, J87.4, R108.1, U22.5
SCL22: J89.4, J90.4, J91.4, R113.1, U23.5
SCL23: J93.4, J94.4, J95.4, R118.1, U24.5
SCL24: J97.4, J98.4, J99.4, R123.1, U25.5
SDA: J1.3, J2.3, J4.3, R1.1, U1.8
SDA1: J5.3, J6.3, J7.3, R7.1, U2.8
SDA2: J9.3, J10.3, J11.3, R12.1, U3.8
SDA3: J13.3, J14.3, J15.3, R17.1, U4.8
SDA4: J17.3, J18.3, J19.3, R22.1, U5.8
SDA5: J21.3, J22.3, J23.3, R27.1, U6.8
SDA6: J25.3, J26.3, J27.3, R32.1, U7.8
SDA7: J29.3, J30.3, J31.3, R37.1, U8.8
SDA8: J33.3, J34.3, J35.3, R42.1, U9.8
SDA9: J37.3, J38.3, J39.3, R47.1, U10.8
SDA10: J41.3, J42.3, J43.3, R52.1, U11.8
SDA11: J45.3, J46.3, J47.3, R57.1, U12.8
SDA12: J49.3, J50.3, J51.3, R62.1, U13.8
SDA13: J53.3, J54.3, J55.3, R67.1, U14.8
SDA14: J57.3, J58.3, J59.3, R72.1, U15.8
SDA15: J61.3, J62.3, J63.3, R77.1, U16.8
SDA16: J65.3, J66.3, J67.3, R82.1, U17.8
SDA17: J69.3, J70.3, J71.3, R87.1, U18.8
SDA18: J73.3, J74.3, J75.3, R92.1, U19.8
SDA19: J77.3, J78.3, J79.3, R97.1, U20.8
SDA20: J81.3, J82.3, J83.3, R102.1, U21.8
SDA21: J85.3, J86.3, J87.3, R107.1, U22.8
SDA22: J89.3, J90.3, J91.3, R112.1, U23.8
SDA23: J93.3, J94.3, J95.3, R117.1, U24.8
SDA24: J97.3, J98.3, J99.3, R122.1, U25.8

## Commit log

2021-01-19 Change IRQ to INT. Add Address label.
2021-01-19 Update library link
2021-01-20 Adding the new PROD_IDs
2021-02-04 Adding the SKU
2021-04-17 Add product image
2022-08-10 Update PROD_IDs. Delete New-Parts

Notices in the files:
parts and their libraries:
SparkFun-Resistors: Licensing: Creative Commons ShareAlike 4.0 International - https://creativecommons.org/licenses/by-sa/4.0
SparkFun-Aesthetics: Released under the Creative Commons Attribution Share-Alike 4.0 License
SparkFun-Aesthetics: https://creativecommons.org/licenses/by-sa/4.0
